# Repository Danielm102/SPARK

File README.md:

# SPARK
Stepper Power And Regulation Kit

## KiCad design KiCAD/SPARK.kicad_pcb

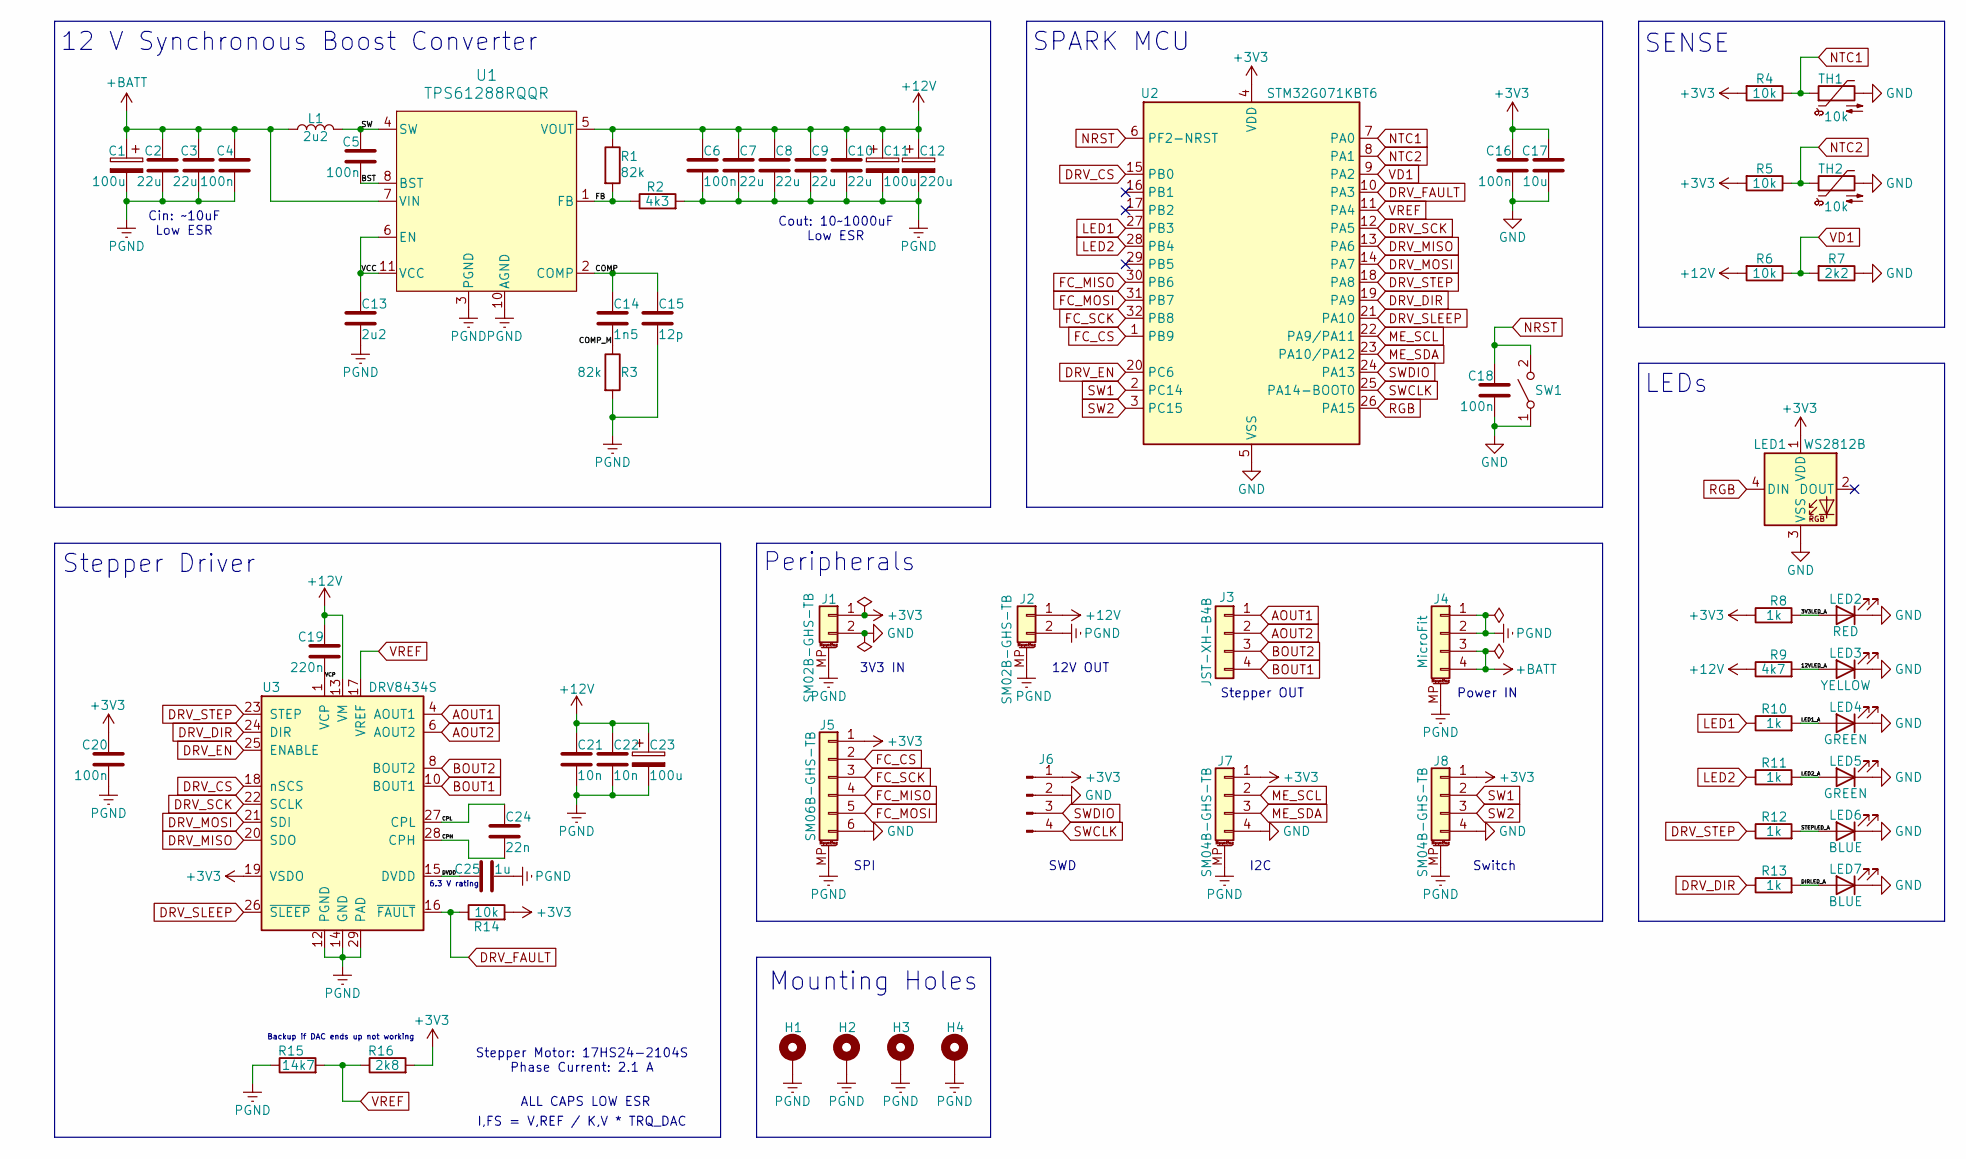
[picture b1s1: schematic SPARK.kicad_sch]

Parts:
C1, C11, C23: 100u; CP_Radial_D5.0mm_P2.00mm
C2, C3, C7, C8, C9, C10: 22u; C_1206_3216Metric
C4, C5, C6, C16, C18, C20: 100n; C_0402_1005Metric
C12: 220u; CP_Radial_D6.3mm_P2.50mm
C13: 2u2; C_0402_1005Metric
C14: 1n5; C_0402_1005Metric
C15: 12p; C_0402_1005Metric
C17: 10u; C_0805_2012Metric
C19: 220n; C_0402_1005Metric
C21, C22: 10n; C_0402_1005Metric
C24: 22n; C_0402_1005Metric
C25: 1u; C_0603_1608Metric
H1, H2, H3, H4: MountingHole_Pad; MountingHole_2.2mm_M2_Pad_Via
J1, J2: SM02B-GHS-TB; JST_GH_SM02B-GHS-TB_1x02-1MP_P1.25mm_Horizontal
J3: JST-XH-B4B; JST_XH_B4B-XH-A_1x04_P2.50mm_Vertical
J4: MicroFit; Molex_Micro-Fit_3.0_43045-0410_2x02-1MP_P3.00mm_Horizontal
J5: SM06B-GHS-TB; JST_GH_SM06B-GHS-TB_1x06-1MP_P1.25mm_Horizontal
J6: Conn_01x04_Pin; PinHeader_1x04_P2.54mm_Vertical
J7, J8: SM04B-GHS-TB; JST_GH_SM04B-GHS-TB_1x04-1MP_P1.25mm_Horizontal
L1: 2u2; L_13.5x12.8
LED1: WS2812B; LED_WS2812B_PLCC4_5.0x5.0mm_P3.2mm
LED2: RED; LED_0603_1608Metric
LED3: YELLOW; LED_0603_1608Metric
LED4, LED5: GREEN; LED_0603_1608Metric
LED6, LED7: BLUE; LED_0603_1608Metric
R1, R3: 82k; R_0402_1005Metric
R2: 4k3; R_0402_1005Metric
R4, R5, R6, R14: 10k; R_0402_1005Metric
R7: 2k2; R_0402_1005Metric
R8, R10, R11, R12, R13: 1k; R_0402_1005Metric
R9: 4k7; R_0402_1005Metric
R15: 14k7; R_0402_1005Metric
R16: 2k8; R_0402_1005Metric
SW1: SW_SPST; Panasonic_EVQPUL_EVQPUC
TH1, TH2: 10k; R_0603_1608Metric
U1: TPS61288RQQR; Texas_VQFN-HR-20_3x2.5mm_P0.5mm_RQQ0011A
U2: STM32G071KBT6; LQFP-32_7x7mm_P0.8mm
U3: DRV8434S; HTSSOP-28-1EP_4.4x9.7mm_P0.65mm_EP3.1x4.05mm_ThermalVias

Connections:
+3V3: C16.1, C17.1, C20.1, J1.1, J5.1, J6.1, J7.1, J8.1, LED1.1 (VDD), R4.2, R5.2, R8.1, R14.2, R16.2, U2.4 (VDD), U3.19 (VSDO)
+12V: C6.1, C7.1, C8.1, C9.1, C10.1, C11.1, C12.1, C19.1, C21.1, C22.1, C23.1, J2.1, R1.1, R6.2, R9.1, U1.5 (VOUT), U3.2 (VM), U3.13 (VM)
+BATT: C1.1, C2.1, C3.1, C4.1, J4.3, J4.4, L1.1, U1.7 (VIN)
/3V3LED_A: LED2.2 (A), R8.2
/12VLED_A: LED3.2 (A), R9.2
/BST: C5.2, U1.8 (BST)
/COMP: C14.1, C15.1, U1.2 (COMP)
/COMP_M: C14.2, R3.1
/CPH: C24.2, U3.28 (CPH)
/CPL: C24.1, U3.27 (CPL)
/DIRLED_A: LED7.2 (A), R13.2
/DVDD: C25.1, U3.15 (DVDD)
/FB: R1.2, R2.1, U1.1 (FB)
/LED1_A: LED4.2 (A), R10.2
/LED2_A: LED5.2 (A), R11.2
/STEPLED_A: LED6.2 (A), R12.2
/SW: C5.1, L1.2, U1.4 (SW), U1.9 (SW)
/VCC: C13.1, U1.6 (EN), U1.11 (VCC)
/VCP: C19.2, U3.1 (VCP)
AOUT1: J3.1, U3.4 (AOUT1), U3.5 (AOUT1)
AOUT2: J3.2, U3.6 (AOUT2), U3.7 (AOUT2)
BOUT1: J3.4, U3.10 (BOUT1), U3.11 (BOUT1)
BOUT2: J3.3, U3.8 (BOUT2), U3.9 (BOUT2)
DRV_CS: U2.15 (PB0), U3.18 (nSCS)
DRV_DIR: R13.1, U2.19 (PA9), U3.24 (DIR)
DRV_EN: U2.20 (PC6), U3.25 (ENABLE)
DRV_FAULT: R14.1, U2.10 (PA3), U3.16 (~FAULT)
DRV_MISO: U2.13 (PA6), U3.20 (SDO)
DRV_MOSI: U2.14 (PA7), U3.21 (SDI)
DRV_SCK: U2.12 (PA5), U3.22 (SCLK)
DRV_SLEEP: U2.21 (PA10), U3.26 (~SLEEP)
DRV_STEP: R12.1, U2.18 (PA8), U3.23 (STEP)
FC_CS: J5.2, U2.1 (PB9)
FC_MISO: J5.4, U2.30 (PB6)
FC_MOSI: J5.5, U2.31 (PB7)
FC_SCK: J5.3, U2.32 (PB8)
GND: C16.2, C17.2, C18.2, J1.2, J5.6, J6.2, J7.4, J8.4, LED1.3 (VSS), LED2.1 (K), LED3.1 (K), LED4.1 (K), LED5.1 (K), LED6.1 (K), LED7.1 (K), R7.1, SW1.1 (A), TH1.2, TH2.2, U2.5 (VSS)
LED1: R10.1, U2.27 (PB3)
LED2: R11.1, U2.28 (PB4)
ME_SCL: J7.2, U2.22 (PA9/PA11)
ME_SDA: J7.3, U2.23 (PA10/PA12)
NRST: C18.1, SW1.2 (B), U2.6 (PF2-NRST)
NTC1: R4.1, TH1.1, U2.7 (PA0)
NTC2: R5.1, TH2.1, U2.8 (PA1)
PGND: C1.2, C2.2, C3.2, C4.2, C6.2, C7.2, C8.2, C9.2, C10.2, C11.2, C12.2, C13.2, C15.2, C20.2, C21.2, C22.2, C23.2, C25.2, H1.1, H2.1, H3.1, H4.1, J1.MP (MountPin), J2.2, J2.MP (MountPin), J4.1, J4.2, J4.MP (MountPin), J5.MP (MountPin), J7.MP (MountPin), J8.MP (MountPin), R2.2, R3.2, R15.1, U1.3 (PGND), U1.10 (AGND), U3.3 (PGND), U3.12 (PGND), U3.14 (GND), U3.29 (PAD)
RGB: LED1.4 (DIN), U2.26 (PA15)
SW1: J8.2, U2.2 (PC14)
SW2: J8.3, U2.3 (PC15)
SWCLK: J6.4, U2.25 (PA14-BOOT0)
SWDIO: J6.3, U2.24 (PA13)
VD1: R6.1, R7.2, U2.9 (PA2)
VREF: R15.2, R16.1, U2.11 (PA4), U3.17 (VREF)

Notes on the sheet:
Peripherals
ALL CAPS LOW ESR
Stepper OUT
Mounting Holes
I,FS = V,REF / K,V * TRQ_DAC
3V3 IN
Power IN
I2C
SENSE
12V OUT
Cin: ~10uF Low ESR
SPI
SWD
SPARK MCU
Stepper Driver
LEDs
6.3 V rating
Stepper Motor: 17HS24-2104S Phase Current: 2.1 A
12 V Synchronous Boost Converter
Cout: 10~1000uF Low ESR
Switch
Backup if DAC ends up not working

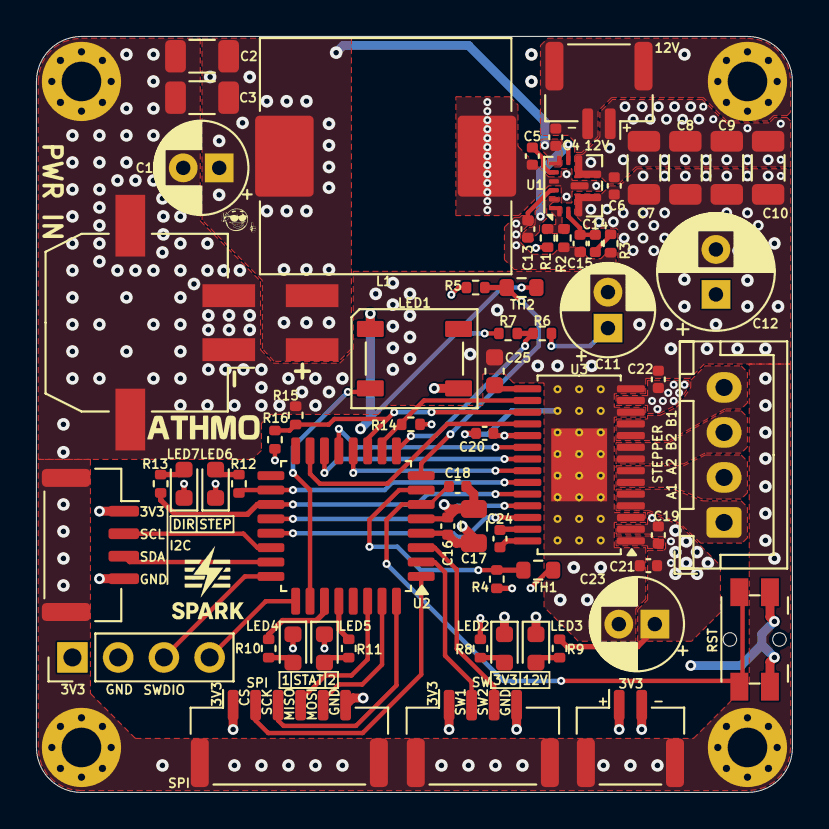
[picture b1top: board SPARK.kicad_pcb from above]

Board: 4 copper layers, 42.0 x 42.0 mm, 67 parts (0 on the bottom side), 52 nets.

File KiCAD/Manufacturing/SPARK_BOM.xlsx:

Reference | Qty | Value | Footprint
C1,C11,C23 | 3 | 100u | Capacitor_THT:CP_Radial_D5.0mm_P2.00mm
C2,C3,C7,C8,C9,C10 | 6 | 22u | Capacitor_SMD:C_1206_3216Metric
C4,C5,C6,C16,C18,C20 | 6 | 100n | Capacitor_SMD:C_0402_1005Metric
C12 | 1 | 220u | Capacitor_THT:CP_Radial_D6.3mm_P2.50mm
C13 | 1 | 2u2 | Capacitor_SMD:C_0402_1005Metric
C14 | 1 | 1n5 | Capacitor_SMD:C_0402_1005Metric
C15 | 1 | 12p | Capacitor_SMD:C_0402_1005Metric
C17 | 1 | 10u | Capacitor_SMD:C_0805_2012Metric
C19 | 1 | 220n | Capacitor_SMD:C_0402_1005Metric
C21,C22 | 2 | 10n | Capacitor_SMD:C_0402_1005Metric
C24 | 1 | 22n | Capacitor_SMD:C_0402_1005Metric
C25 | 1 | 1u | Capacitor_SMD:C_0603_1608Metric
J1,J2 | 2 | SM02B-GHS-TB | Connector_JST:JST_GH_SM02B-GHS-TB_1x02-1MP_P1.25mm_Horizontal
J3 | 1 | JST-XH-B4B | Connector_JST:JST_XH_B4B-XH-A_1x04_P2.50mm_Vertical
J4 | 1 | MicroFit | Connector_Molex:Molex_Micro-Fit_3.0_43045-0410_2x02-1MP_P3.00mm_Horizontal
J5 | 1 | SM06B-GHS-TB | Connector_JST:JST_GH_SM06B-GHS-TB_1x06-1MP_P1.25mm_Horizontal
J7,J8 | 2 | SM04B-GHS-TB | Connector_JST:JST_GH_SM04B-GHS-TB_1x04-1MP_P1.25mm_Horizontal
L1 | 1 | 2u2 | Library:L_13.5x12.8
LED1 | 1 | WS2812B | LED_SMD:LED_WS2812B_PLCC4_5.0x5.0mm_P3.2mm
LED2 | 1 | RED | LED_SMD:LED_0603_1608Metric
LED3 | 1 | YELLOW | LED_SMD:LED_0603_1608Metric
LED4,LED5 | 2 | GREEN | LED_SMD:LED_0603_1608Metric
LED6,LED7 | 2 | BLUE | LED_SMD:LED_0603_1608Metric
R1,R3 | 2 | 82k | Resistor_SMD:R_0402_1005Metric
R2 | 1 | 4k3 | Resistor_SMD:R_0402_1005Metric
R4,R5,R6,R14 | 4 | 10k | Resistor_SMD:R_0402_1005Metric
R7 | 1 | 2k2 | Resistor_SMD:R_0402_1005Metric
R8,R10,R11,R12,R13 | 5 | 1k | Resistor_SMD:R_0402_1005Metric
R9 | 1 | 4k7 | Resistor_SMD:R_0402_1005Metric
R15 | 1 | 14k7 | Resistor_SMD:R_0402_1005Metric
R16 | 1 | 2k8 | Resistor_SMD:R_0402_1005Metric
SW1 | 1 | SW_SPST | Button_Switch_SMD:Panasonic_EVQPUL_EVQPUC
TH1,TH2 | 2 | 10k | Resistor_SMD:R_0603_1608Metric
U1 | 1 | TPS61288RQQR | Package_DFN_QFN:Texas_VQFN-HR-20_3x2.5mm_P0.5mm_RQQ0011A
U2 | 1 | STM32G071KBT6 | Package_QFP:LQFP-32_7x7mm_P0.8mm
U3 | 1 | DRV8434S | Library:HTSSOP-28-1EP_4.4x9.7mm_P0.65mm_EP3.1x4.05mm_ThermalVias

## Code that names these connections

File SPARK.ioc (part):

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Mcu.Name=STM32G071K(6-8-B)Tx
Mcu.Package=LQFP32
Mcu.UserName=STM32G071KBTx
PA0.GPIOParameters=GPIO_Label
PA0.GPIO_Label=NTC1
PA0.Mode=IN0
PA0.Signal=ADC1_IN0
PA1.GPIOParameters=GPIO_Label
PA1.GPIO_Label=NTC2
PA1.Mode=IN1
PA1.Signal=ADC1_IN1
PA10.GPIOParameters=GPIO_Label
PA10.GPIO_Label=DRV_SLEEP
PA10.Signal=GPIO_Output
PA11\ [PA9].GPIOParameters=GPIO_Speed,GPIO_Pu
PA11\ [PA9].GPIO_Pu=GPIO_PULLUP
PA11\ [PA9].GPIO_Speed=GPIO_SPEED_FREQ_VERY_HIGH
PA11\ [PA9].Mode=I2C
PA11\ [PA9].Signal=I2C2_SCL
PA12\ [PA10].GPIOParameters=GPIO_Speed,GPIO_Pu
PA12\ [PA10].GPIO_Pu=GPIO_PULLUP
PA12\ [PA10].GPIO_Speed=GPIO_SPEED_FREQ_VERY_HIGH
PA12\ [PA10].Mode=I2C
PA12\ [PA10].Signal=I2C2_SDA
PA13.Mode=Serial_Wire
PA13.Signal=SYS_SWDIO
PA14-BOOT0.Mode=Serial_Wire
PA14-BOOT0.Signal=SYS_SWCLK
PA15.GPIOParameters=GPIO_Speed,GPIO_Label
PA15.GPIO_Label=RGB
PA15.GPIO_Speed=GPIO_SPEED_FREQ_VERY_HIGH
PA15.Signal=S_TIM2_CH1_ETR
PA2.GPIOParameters=GPIO_Label
PA2.GPIO_Label=VD1
PA2.Mode=IN2
PA2.Signal=ADC1_IN2
PA3.GPIOParameters=GPIO_Label,GPIO_ModeDefaultEXTI
PA3.GPIO_Label=DRV_FAULT
PA3.GPIO_ModeDefaultEXTI=GPIO_MODE_IT_FALLING
PA3.Signal=GPXTI3
PA4.GPIOParameters=GPIO_Label
PA4.GPIO_Label=DRV_VREF
PA4.Signal=COMP_DAC11_group
PA5.GPIOParameters=GPIO_Speed
PA5.GPIO_Speed=GPIO_SPEED_FREQ_VERY_HIGH
PA5.Mode=Full_Duplex_Master
PA5.Signal=SPI1_SCK
PA6.GPIOParameters=GPIO_Speed
PA6.GPIO_Speed=GPIO_SPEED_FREQ_VERY_HIGH
PA6.Mode=Full_Duplex_Master
PA6.Signal=SPI1_MISO
PA7.GPIOParameters=GPIO_Speed
PA7.GPIO_Speed=GPIO_SPEED_FREQ_VERY_HIGH
PA7.Mode=Full_Duplex_Master
PA7.Signal=SPI1_MOSI
PA8.GPIOParameters=GPIO_Speed,GPIO_Label
PA8.GPIO_Label=DRV_STEP
PA8.GPIO_Speed=GPIO_SPEED_FREQ_VERY_HIGH
PA8.Signal=S_TIM1_CH1
PA9.GPIOParameters=GPIO_PuPd,GPIO_Label,GPIO_ModeDefaultOutputPP
PA9.GPIO_Label=DRV_DIR
PA9.GPIO_ModeDefaultOutputPP=GPIO_MODE_OUTPUT_PP
PA9.GPIO_PuPd=GPIO_NOPULL
PA9.Signal=GPIO_Output
PB0.GPIOParameters=PinState,GPIO_PuPd,GPIO_Label,GPIO_ModeDefaultOutputPP
PB0.GPIO_Label=DRV_CS
PB0.GPIO_ModeDefaultOutputPP=GPIO_MODE_OUTPUT_OD
PB0.GPIO_PuPd=GPIO_NOPULL
PB0.PinState=GPIO_PIN_SET
PB0.Signal=GPIO_Output
PB3.GPIOParameters=PinState,GPIO_Label
PB3.GPIO_Label=LED1
PB3.PinState=GPIO_PIN_SET
PB3.Signal=GPIO_Output
PB4.GPIOParameters=GPIO_Label
PB4.GPIO_Label=LED2
PB4.Signal=GPIO_Output
PB6.GPIOParameters=GPIO_Speed,GPIO_Label
PB6.GPIO_Label=FC_MISO
PB6.GPIO_Speed=GPIO_SPEED_FREQ_VERY_HIGH
PB6.Mode=Full_Duplex_Slave
PB6.Signal=SPI2_MISO
PB7.GPIOParameters=GPIO_Speed,GPIO_Label
PB7.GPIO_Label=FC_MOSI
PB7.GPIO_Speed=GPIO_SPEED_FREQ_VERY_HIGH
PB7.Mode=Full_Duplex_Slave
PB7.Signal=SPI2_MOSI
PB8.GPIOParameters=GPIO_Speed,GPIO_Label
PB8.GPIO_Label=FC_SCK
PB8.GPIO_Speed=GPIO_SPEED_FREQ_VERY_HIGH
PB8.Mode=Full_Duplex_Slave
PB8.Signal=SPI2_SCK
PB9.GPIOParameters=GPIO_Label
PB9.GPIO_Label=FC_CS
PB9.Signal=GPXTI9
PC14-OSC32_IN\ (PC14).GPIOParameters=GPIO_Label
PC14-OSC32_IN\ (PC14).GPIO_Label=SW1
PC14-OSC32_IN\ (PC14).Signal=GPXTI14
PC15-OSC32_OUT\ (PC15).GPIOParameters=GPIO_Label
PC15-OSC32_OUT\ (PC15).GPIO_Label=SW2
PC15-OSC32_OUT\ (PC15).Signal=GPXTI15
PC6.GPIOParameters=GPIO_PuPd,GPIO_Label,GPIO_ModeDefaultOutputPP
PC6.GPIO_Label=DRV_EN
PC6.GPIO_ModeDefaultOutputPP=GPIO_MODE_OUTPUT_PP
PC6.GPIO_PuPd=GPIO_NOPULL
PC6.Signal=GPIO_Output
RCC.HSE_VALUE=8000000
RCC.SYSCLKFreq_VALUE=16000000
board=custom

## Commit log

2025-09-06 Code generated
2025-09-06 Basic uploading and execution working
2025-09-06 RGB LED + status library
2025-09-06 DRV8434S library (in progress)
2025-09-07 Timing adjustments
2025-09-07 Added fault detection
2025-09-07 DRV8434S SPI library added
    Prototype. Most functions not yet tested.
2025-09-08 Stepper init and pwm burst function added
2025-09-08 Loops added
    10 Hz, 100 Hz & 1000 Hz
2025-09-09 AS5600 library added
2025-09-10 Stepper homing sequence
2025-09-11 Timer small frequency bug fixed
2025-09-12 Stepper stall learning sequence
2025-09-12 Homing sequence working
2025-09-15 Homing sequence improved
2025-10-05 Basic communication with FC
2025-10-12 State Machine library added
2025-10-12 TIM7 used for forcing events
2025-10-21 ACS Math added, states added
2025-10-21 Zeroing moved to State Machine
2025-10-22 Init & Startup checks
2025-10-22 ACS math moved to GPA Mega primary
2025-10-23 Commands added + Command ID enum
2025-10-30 Fixed stuff
2025-11-05 Fixed startup issue.
    Fixed issue where Stepper_init(); was called while ACS disarmed, which caused the microstepping settings resetting after arming
2025-11-05 Fixed fault clearing loops.
    Fixed issue where fault pin would rise immediately after clearing a fault, causing another clear, resulting in the microcontroller being stuck
2025-11-09 Fixed accidental rotation count during startup
    Just so the rotation count variable makes sense
2025-11-10 Fixed RGB LED
2025-11-11 ACS control and monitoring
2025-11-11 PD controller
2025-11-12 Implemented crc check for commands, removed position margin
2025-11-27 Adjusted sign convention
